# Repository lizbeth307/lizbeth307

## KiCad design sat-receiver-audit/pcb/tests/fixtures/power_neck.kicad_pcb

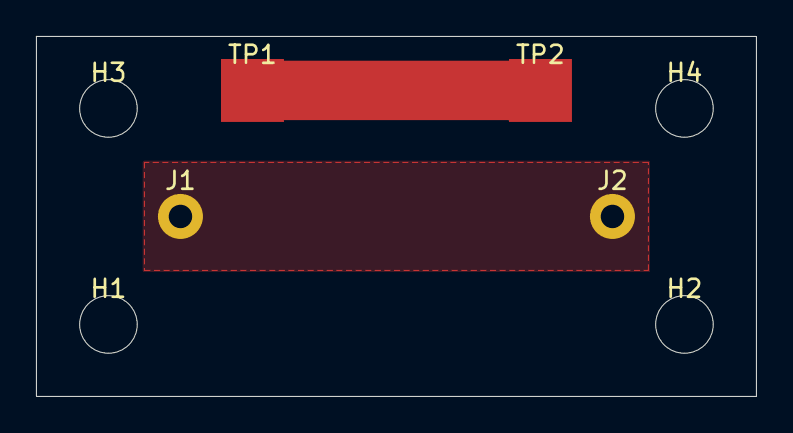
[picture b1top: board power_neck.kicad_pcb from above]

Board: 4 copper layers, 40.0 x 20.0 mm, 8 parts (0 on the bottom side), 2 nets.

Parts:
H1, H2, H3, H4: MountingHole_3.2mm_M3
J1, J2: TERM_THT_1x01
TP1, TP2: PAD_SMD_3.5

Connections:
E1_N: TP1.1, TP2.1
E1_SHUNT_P: J1.1, J2.1

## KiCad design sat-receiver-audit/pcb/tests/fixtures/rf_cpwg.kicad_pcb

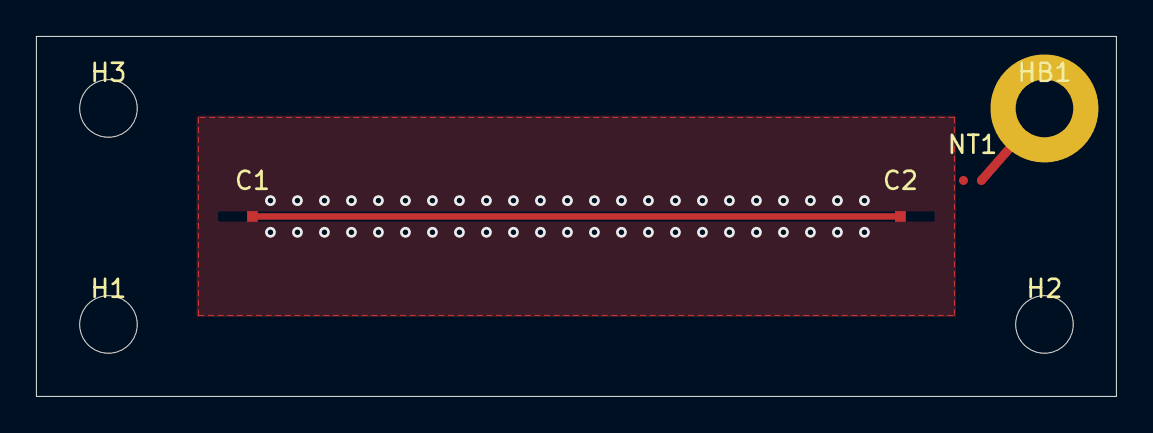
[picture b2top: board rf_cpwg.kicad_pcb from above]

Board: 4 copper layers, 60.0 x 20.0 mm, 7 parts (0 on the bottom side), 2 nets.

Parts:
C1, C2: PAD_RF
H1, H2, H3: MountingHole_3.2mm_M3
HB1: MountingHole_3.2mm_M3_Pad
NT1: NetTie-2_SMD_Pad0.5mm

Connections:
CHASSIS: HB1.1, NT1.2
E4_RTLA_RF1: C1.1, C2.1
